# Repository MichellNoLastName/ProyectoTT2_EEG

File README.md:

# EEG con Sensores Capacitivos de No Contacto

## 🧠 Descripción

Este proyecto consiste en el desarrollo de un prototipo para la adquisición de señales electroencefalográficas (EEG) utilizando sensores capacitivos de no contacto. El sistema incluye una interfaz gráfica desarrollada en LabVIEW que permite visualizar y guardar los datos adquiridos.

El propósito principal es contar con una alternativa no invasiva y cómoda para el monitoreo de actividad cerebral, útil para investigación biomédica y futuros desarrollos en interfaces cerebro-computadora.

## 🔧 Tecnologías utilizadas

- **Lenguaje C** – Programación de microcontroladores.
- **Arduino** – Pruebas iniciales y prototipado.
- **MPLAB X IDE** – Desarrollo en microcontroladores PIC.
- **LabVIEW** – Interfaz gráfica para visualización y almacenamiento de señales.
- **SolidWorks** – Diseño del headset 3D.
- **Autodesk EAGLE** – Diseño de las placas electrónicas.

## 🖼️ Capturas

### Placa electrónica del electrodo en 3D Vista superior

### Placa electrónica del electrodo en 3D Vista inferior

### Placa electrónica del electrodo fabricada

### Headset impreso en 3D

## Pruebas realizadas

### Interfaz de LabVIEW

## 🚀 Instrucciones básicas de uso

1. **Conecta el sistema**: Alimenta los sensores y conecta el microcontrolador al PC.
2. **Ejecuta la interfaz LabVIEW**: Abre el archivo del proyecto y configura el puerto de comunicación.
3. **Adquiere señales**: Visualiza en tiempo real y guarda los datos cuando sea necesario.
4. **Exporta**: Los datos pueden exportarse como archivo `.csv` para análisis posterior.

## 🤝 Contribuciones

Este proyecto es parte de una tesis de ingeniería, pero estás invitado a contribuir con mejoras, sugerencias o ideas. Abre un Issue o un Pull Request si deseas colaborar.

## 🧾 Licencia

Este proyecto no tiene una licencia formal asignada. Si deseas usarlo con fines educativos o de investigación, puedes hacerlo con atribución.

## 👤 Autor

Michell Alejandro López Sierra  
[GitHub](https://github.com/) | [LinkedIn](https://linkedin.com/) | [Email](ingmichell5101@gmail.com)

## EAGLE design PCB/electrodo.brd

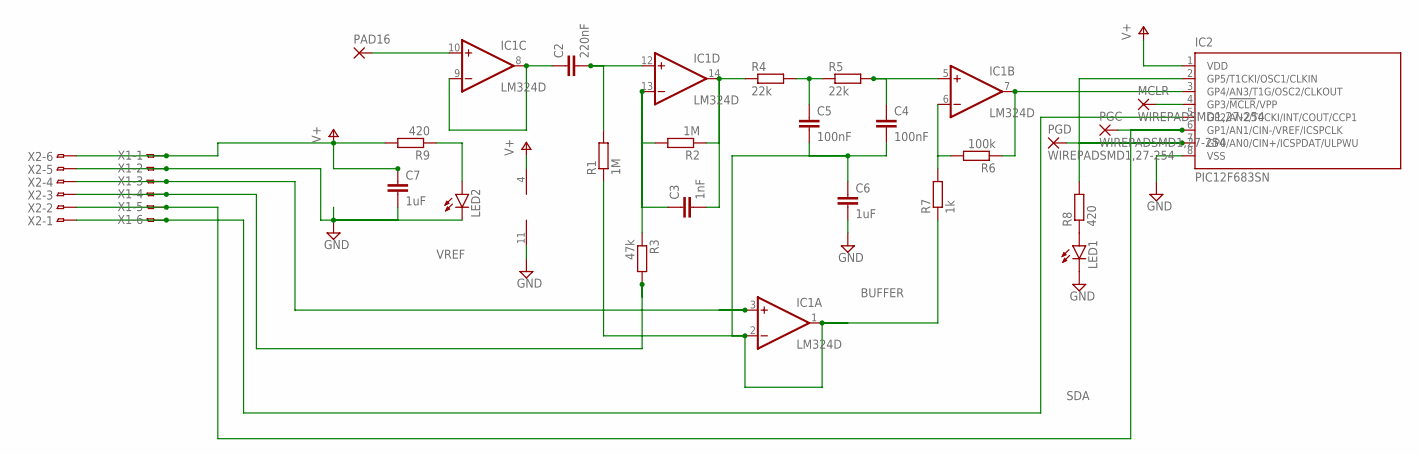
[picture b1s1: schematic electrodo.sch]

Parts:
C2: 220nF; C0603
C3: 1nF; C0603
C4, C5: 100nF; C0603
C6, C7: 1uF; C0603
IC1: LM324D; SO14
IC2: PIC12F683SN; SO-08
LED1, LED2: LEDSML0805; SML0805
MCLR: WIREPADSMD1,27-254; SMD1,27-2,54
PAD16: 1,6/0,9
PGC: WIREPADSMD1,27-254; SMD1,27-2,54
PGD: WIREPADSMD1,27-254; SMD1,27-2,54
R1, R2: 1M; R0603
R3: 47k; R0603
R4, R5: 22k; R0603
R6: 100k; R0603
R7: 1k; R0603
R8, R9: 420; R0603
X1, X2: FH12-08S-1SH

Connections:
BUFFER: C4.2, C5.2, C6.1, IC1.1 (OUT), IC1.2 (-IN), R1.1, R7.1
GND: C6.2, C7.2, IC1.11 (V-), IC2.8 (VSS), LED1.C, LED2.C, X1.2, X2.5
unnamed: IC2.2 (GP5/T1CKI/OSC1/CLKIN), R8.2
unnamed: C4.1, IC1.5 (+IN), R5.2
unnamed: C2.2, IC1.12 (+IN), R1.2
unnamed: IC1.7 (OUT), IC2.3 (GP4/AN3/T1G/OSC2/CLKOUT), R6.1
unnamed: LED1.A, R8.1
unnamed: C3.2, IC1.14 (OUT), R2.1, R4.1
unnamed: LED2.A, R9.1
unnamed: IC2.4 (GP3/!MCLR!/VPP), MCLR.1
unnamed: C5.1, R4.2, R5.1
unnamed: IC1.6 (-IN), R6.2, R7.2
unnamed: IC1.10 (+IN), PAD16.1
unnamed: C2.1, IC1.8 (OUT), IC1.9 (-IN)
unnamed: C3.1, IC1.13 (-IN), R2.2, R3.1
unnamed: IC2.7 (GP0/AN0/CIN+/ICSPDAT/ULPWU), PGD.1
REFGROUND: R3.2, X1.4, X2.3
SCL: IC2.6 (GP1/AN1/CIN-/VREF/ICSPCLK), PGC.1, X1.5, X2.2
SDA: IC2.5 (GP2/AN2/T0CKI/INT/COUT/CCP1), X1.6, X2.1
V+: C7.1, IC1.4 (V+), IC2.1 (VDD), R9.2, X1.1, X2.6
VREF: IC1.3 (+IN), X1.3, X2.4

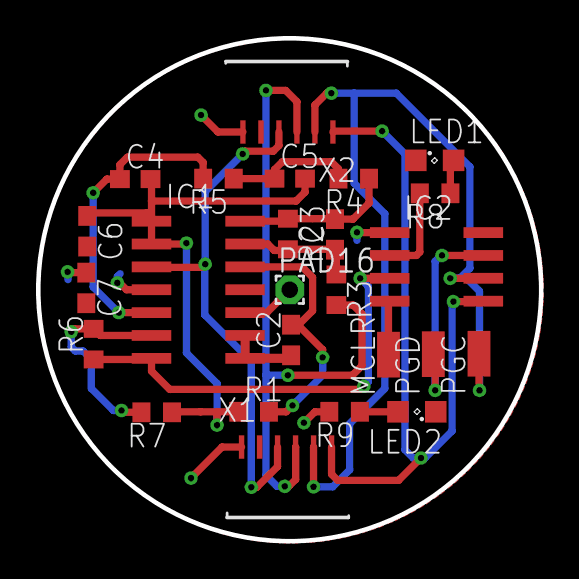
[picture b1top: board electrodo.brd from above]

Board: 2 copper layers, 27.9 x 27.9 mm, 25 parts (0 on the bottom side), 21 nets.

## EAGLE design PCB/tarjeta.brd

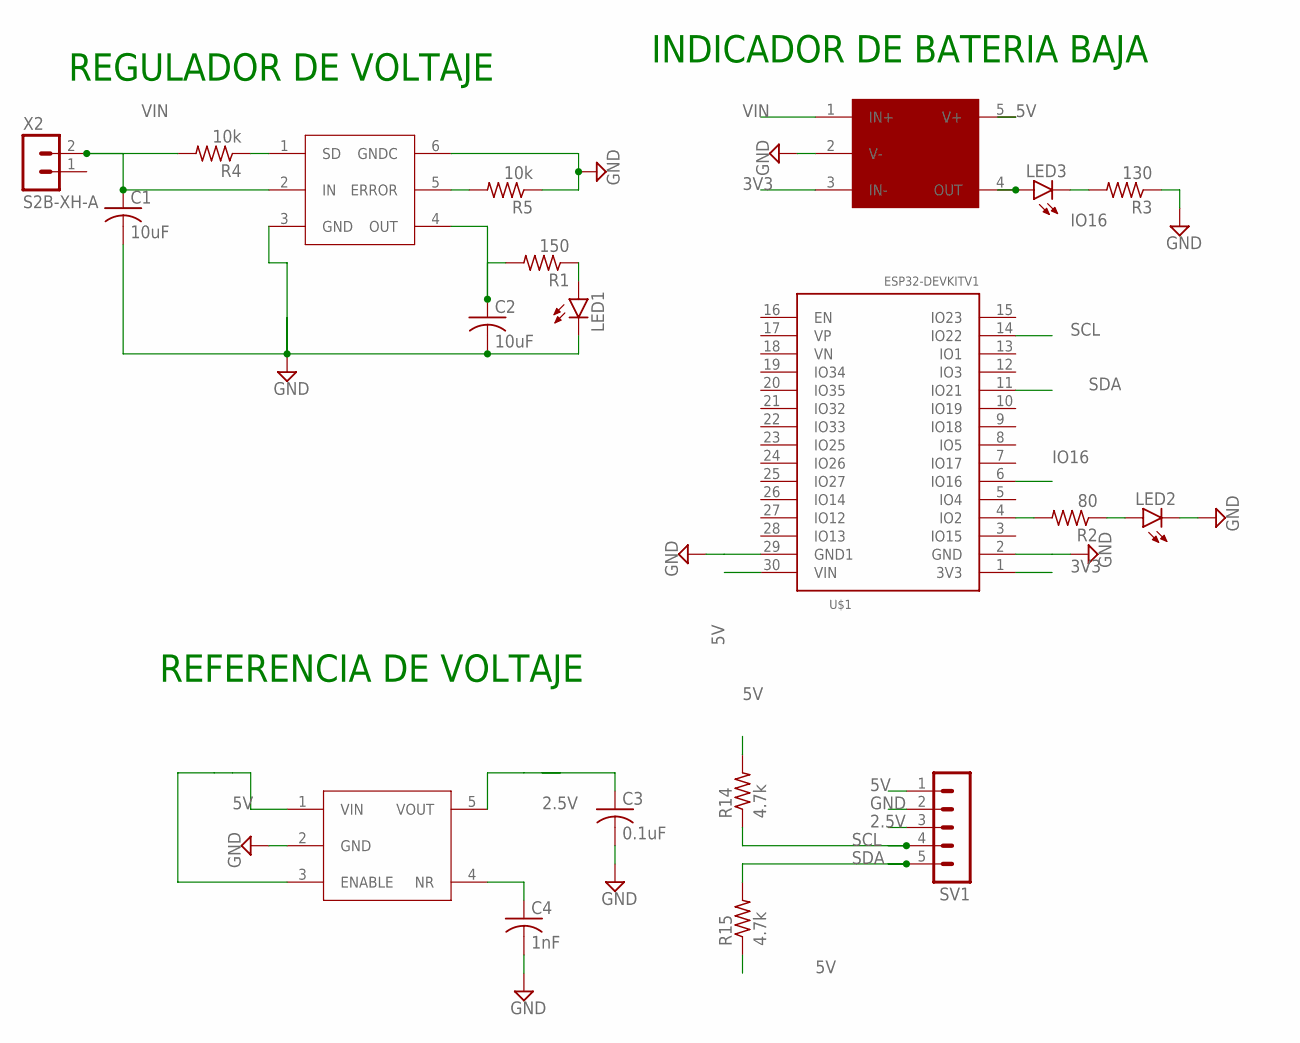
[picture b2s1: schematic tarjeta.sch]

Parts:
.: LP3872ES; TO263-5
C1, C2: 10uF; C0603
C3: 0.1uF; C0603
C4: 1nF; C0603
LED1, LED2, LED3: LEDSML0805; SML0805
R1: 150; R0603
R2: 80; R0603
R3: 130; R0603
R4, R5: 10k; R0603
R14, R15: 4.7k; R0603
SV1: MA05-1
U$1: ESP32DEVKITV1; ESP32-DEVKITV1
U$3: REG113; SOT23-5
U$4: TL081-5; SOT23-5
X2: S2B-XH-A

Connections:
2.5V: C3.1, SV1.3, U$3.5 (VOUT)
3V3: U$1.1 (3V3), U$4.3 (IN-)
5V: R14.2, R15.1, SV1.1, U$1.30 (VIN), U$3.1 (VIN), U$3.3 (ENABLE), U$4.5 (V+)
GND: ..3 (GND), ..6 (GNDC), C1.2, C2.2, C3.2, C4.2, LED1.C, LED2.C, R3.1, R5.1, SV1.2, U$1.2 (GND), U$1.29 (GND1), U$3.2 (GND), U$4.2 (V-)
IO16: LED3.C, R3.2, U$1.6 (IO16)
unnamed: LED1.A, R1.1
unnamed: LED3.A, U$4.4 (OUT)
unnamed: R2.2, U$1.4 (IO2)
unnamed: LED2.A, R2.1
unnamed: ..1 (SD), R4.1
unnamed: C4.1, U$3.4 (NR)
unnamed: ..5 (ERROR), R5.2
unnamed: ..4 (OUT), C2.1, R1.2
SCL: R14.1, SV1.4, U$1.14 (IO22)
SDA: R15.2, SV1.5, U$1.11 (IO21)
VIN: ..2 (IN), C1.1, R4.2, U$4.1 (IN+), X2.2

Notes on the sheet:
REGULADOR DE VOLTAJE
REFERENCIA DE VOLTAJE
INDICADOR DE BATERIA BAJA

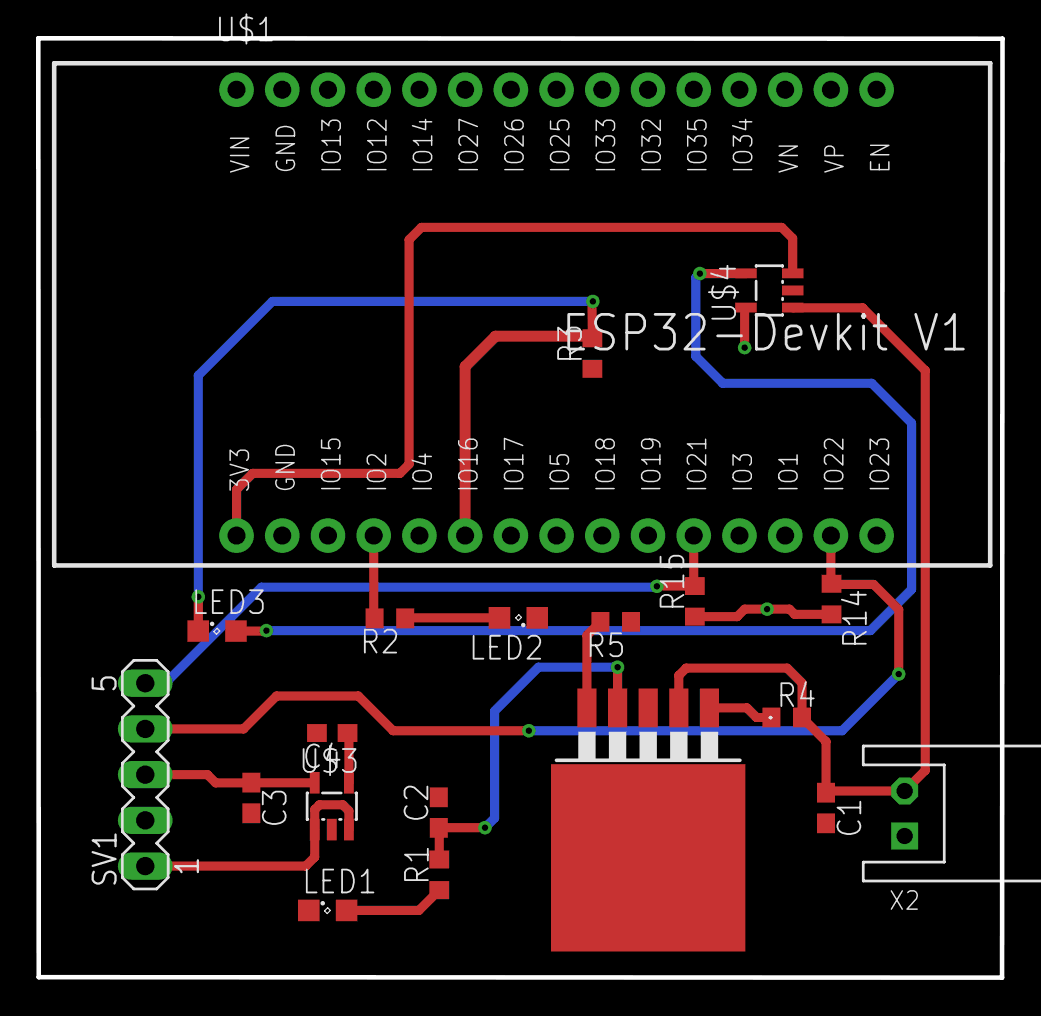
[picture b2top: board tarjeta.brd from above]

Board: 2 copper layers, 53.6 x 52.2 mm, 20 parts (0 on the bottom side), 16 nets.

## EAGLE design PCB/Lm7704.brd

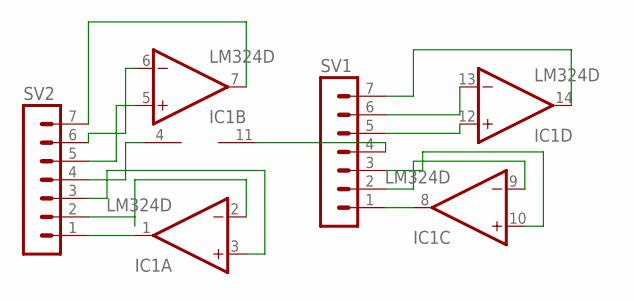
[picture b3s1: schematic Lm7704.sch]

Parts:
IC1: LM324D; SO14
SV1, SV2: MA07-1

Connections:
unnamed: IC1.1 (OUT), SV2.1
unnamed: IC1.2 (-IN), SV2.2
unnamed: IC1.3 (+IN), SV2.3
unnamed: IC1.4 (V+), SV2.4
unnamed: IC1.5 (+IN), SV2.5
unnamed: IC1.6 (-IN), SV2.6
unnamed: IC1.7 (OUT), SV2.7
unnamed: IC1.8 (OUT), SV1.1
unnamed: IC1.9 (-IN), SV1.2
unnamed: IC1.10 (+IN), SV1.3
unnamed: IC1.11 (V-), SV1.4
unnamed: IC1.12 (+IN), SV1.5
unnamed: IC1.13 (-IN), SV1.6
unnamed: IC1.14 (OUT), SV1.7

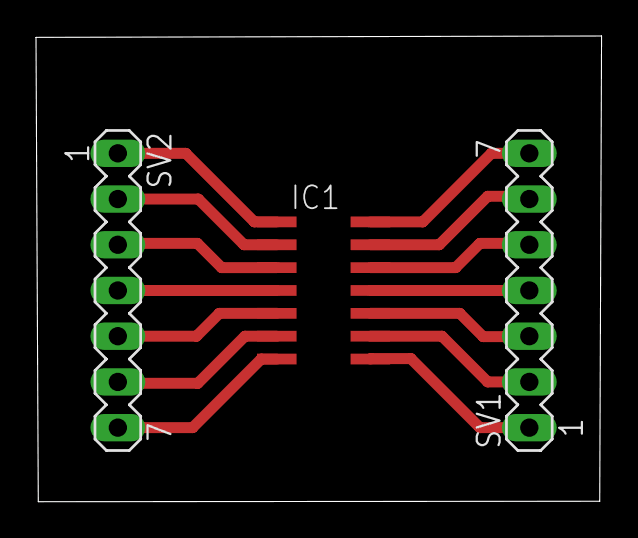
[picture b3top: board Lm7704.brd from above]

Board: 2 copper layers, 31.4 x 25.9 mm, 3 parts (0 on the bottom side), 14 nets.

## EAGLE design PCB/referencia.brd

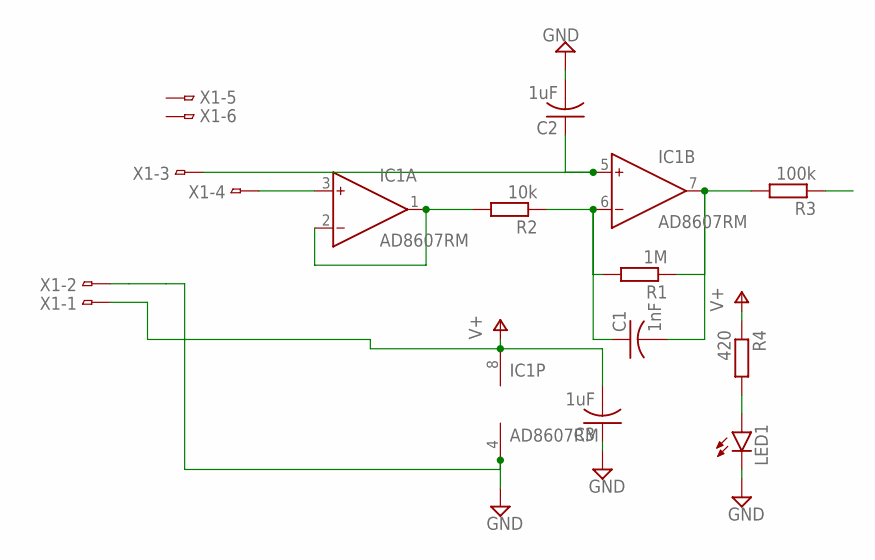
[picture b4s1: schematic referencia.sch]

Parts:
C1: 1nF; C0603
C2, C3: 1uF; C0603
IC1: AD8607RM; MSOP08
LED1: LEDSML0805; SML0805
R1: 1M; R0603
R2: 10k; R0603
R3: 100k; R0603
R4: 420; R0603
X1: FH12-08S-1SH

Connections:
GND: C2.2, C3.1, IC1.4 (V-), LED1.C, X1.2
unnamed: IC1.1 (OUT), IC1.2 (IN-), R2.2
unnamed: C1.1, IC1.6 (IN-), R1.2, R2.1
unnamed: C1.2, IC1.7 (OUT), R1.1, R3.2
unnamed: IC1.3 (IN+), X1.4
unnamed: C2.1, IC1.5 (IN+), X1.3
unnamed: LED1.A, R4.2
REF: R3.1
V+: C3.2, IC1.8 (V+), R4.1, X1.1

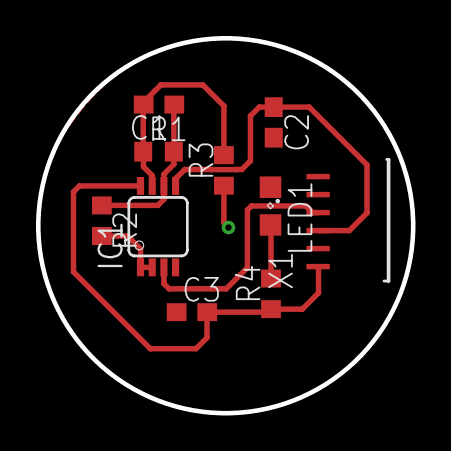
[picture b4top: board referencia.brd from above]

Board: 2 copper layers, 20.8 x 20.8 mm, 10 parts (0 on the bottom side), 8 nets.

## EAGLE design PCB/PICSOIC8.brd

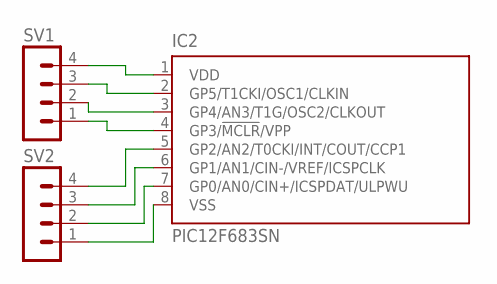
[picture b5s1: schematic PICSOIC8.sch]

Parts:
IC2: PIC12F683SN; SO-08
SV1, SV2: MA04-1

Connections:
unnamed: IC2.1 (VDD), SV1.4
unnamed: IC2.2 (GP5/T1CKI/OSC1/CLKIN), SV1.3
unnamed: IC2.3 (GP4/AN3/T1G/OSC2/CLKOUT), SV1.2
unnamed: IC2.4 (GP3/!MCLR!/VPP), SV1.1
unnamed: IC2.5 (GP2/AN2/T0CKI/INT/COUT/CCP1), SV2.4
unnamed: IC2.6 (GP1/AN1/CIN-/VREF/ICSPCLK), SV2.3
unnamed: IC2.7 (GP0/AN0/CIN+/ICSPDAT/ULPWU), SV2.2
unnamed: IC2.8 (VSS), SV2.1

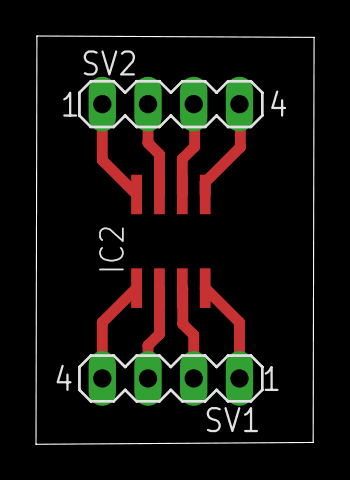
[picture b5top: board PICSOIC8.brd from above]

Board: 2 copper layers, 15.4 x 22.7 mm, 3 parts (0 on the bottom side), 8 nets.

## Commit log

2025-07-08 Version preliminar de EEG
2025-07-10 Version de prueba con implementacion de Queues
2025-07-12 Se comienza construccion de los waveforms
2025-07-12 Se agregan graficas y filtros
2025-07-13 Version preliminar de entrega de proyecto
2025-07-14 Version final de interfaz LabView V1
2025-07-18 Cambio de filtros, integracion de notch y butterworth y smoothhig
2025-07-23 Se configura los electrodos para con una referencia de voltaje de 1.024V
2025-07-23 Se agrega conversion de V a uV
2025-07-24 Version estable
2025-07-24 Se agrega capacidad de guardar la señales
2025-07-24 Version final para presentacion
2025-07-27 Se agregan modelos CAD
2025-07-28 Se agregan imagenes para el README.me
2025-07-28 Creacion de README.md
